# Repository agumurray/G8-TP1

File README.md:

# TdP-Grupo8-2025

**Robot resolutor de laberintos con EDU-CIAA**

Este proyecto consiste en el diseño y construcción de un robot móvil capaz de resolver laberintos físicos con paredes de manera autónoma. El sistema utiliza como controlador principal la **EDU-CIAA**, que gestiona los sensores y motores, y ejecuta algoritmos de navegación para alcanzar la salida sin necesidad de un mapa previo.

## Características principales

* Exploración autónoma de laberintos físicos.
* Algoritmos de resolución basados en estrategias clásicas (wall-following, Pledge, Trémaux).
* Plataforma móvil con dos motores DC controlados mediante un puente H L298N.
* Sensores ultrasónicos para la detección de paredes y obstáculos.
* Posibilidad de extender funcionalidades con:

  * Telemetría mediante ESP32 e interfaz web.
  * Algoritmos de búsqueda óptima (Flood Fill, A*).
  * Sensores adicionales como giroscopio para corrección de trayectoria.

## Tecnologías utilizadas

* **Hardware:**

  * EDU-CIAA (controlador central).
  * Motores DC con puente H L298N.
  * Sensores ultrasónicos HC-SR04.
  * Batería y sistema de alimentación dedicado.
  * (Opcional) ESP32 para telemetría y giroscopio.

* **Software:**

  * Lenguaje C para firmware en la EDU-CIAA.
  * Algoritmos de filtrado de señales y resolución de laberintos.
  * (Opcional) HTML/CSS/JavaScript para interfaz web de monitoreo.

## Objetivos

* **General:** Desarrollar un robot controlado por EDU-CIAA capaz de explorar físicamente un laberinto con paredes y alcanzar la salida mediante estrategias de navegación autónoma.

* **Primarios:**

  1. Diseñar la plataforma mecánica y de potencia (chasis, ruedas, transmisión, alimentación).
  2. Integrar sensado frontal para detección de paredes/obstáculos.
  3. Implementar un algoritmo de resolución de laberintos con información local.
  4. Validar el funcionamiento en laberintos de prueba con métricas definidas.

* **Secundarios:**

  1. Incorporar una interfaz web para recolectar telemetría.
  2. Implementar algoritmos de búsqueda óptima.
  3. Integrar un sensor giroscópico para corrección de maniobras.

## Integrantes

Este proyecto fue desarrollado por el **Grupo 8** en el marco de la materia **Taller de Proyecto I** en la Facultad de Ingeniería de la UNLP:

* Cabral Ramiro Nicolas
* Murray Agustín
* González Juan
* Mendoza Tomás

---

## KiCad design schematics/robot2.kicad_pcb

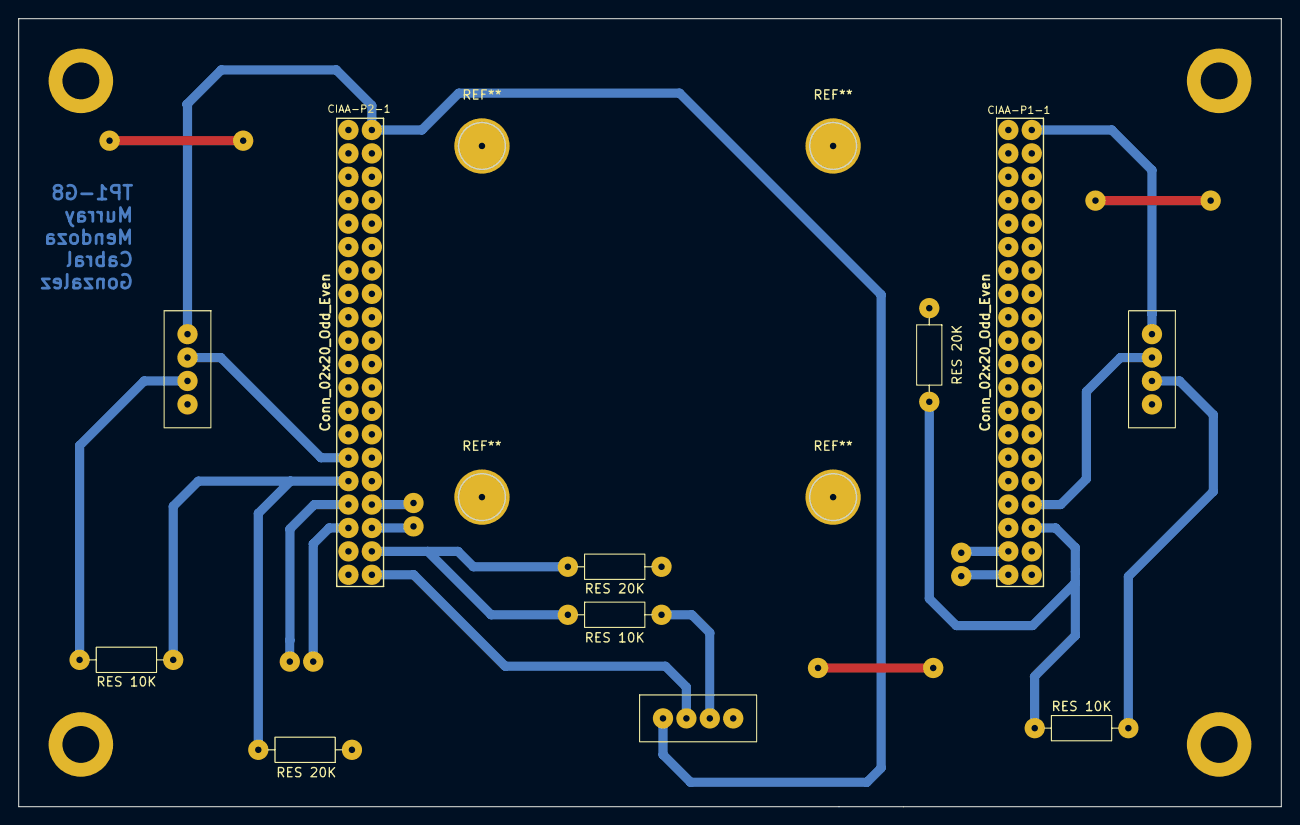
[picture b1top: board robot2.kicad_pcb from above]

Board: 2 copper layers, 137.0 x 85.5 mm, 11 parts (0 on the bottom side), 12 nets.

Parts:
CIAA-P1-1, CIAA-P2-1: Conn_02x20_Odd_Even; PIN_ARRAY_20X2
HC-SR04-1, HC-SR04-2, HC-SR04-3: HC-SR04
R2, R5: 20K; R_Axial_DIN0207_L6.3mm_D2.5mm_P10.16mm_Horizontal
RES 10K, RES 10K#2, RES 10K#3: 10K; R_Axial_DIN0207_L6.3mm_D2.5mm_P10.16mm_Horizontal
RES 20K: 20K; R_Axial_DIN0207_L6.3mm_D2.5mm_P10.16mm_Horizontal

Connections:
5VL: CIAA-P2-1.2 (5V), HC-SR04-1.1 (Vcc), HC-SR04-2.1 (Vcc)
5VR: CIAA-P1-1.2 (5V), HC-SR04-3.1 (Vcc)
GND: CIAA-P1-1.4 (GND), CIAA-P1-1.7 (GNDA), CIAA-P2-1.11 (GND), HC-SR04-1.4 (GND), HC-SR04-2.4 (GND), HC-SR04-3.4 (GND), R2.1, R5.1, RES 20K.1
GPIO0: CIAA-P2-1.29 (GPIO0), HC-SR04-1.2 (Trigger)
GPIO2: CIAA-P2-1.31 (GPIO2), R5.2, RES 10K#2.1
GPIO7: CIAA-P2-1.38 (GPIO7), RES 10K.1, RES 20K.2
GPIO8: CIAA-P2-1.40 (GPIO8), HC-SR04-2.2 (Trigger)
unnamed: HC-SR04-1.3 (Echo), RES 10K#2.2
unnamed: HC-SR04-2.3 (Echo), RES 10K.2
unnamed: HC-SR04-3.3 (Echo), RES 10K#3.2
TCOL2: CIAA-P1-1.34 (TCOL2), HC-SR04-3.2 (Trigger)
TFIL1: CIAA-P1-1.36 (TFIL1), R2.2, RES 10K#3.1

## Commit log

2025-09-25 fixes
2025-09-25 fix readme
2025-09-28 added schematic v2
2025-10-06 drivers hcsr04|l298n
2025-10-07 updated test program
2025-10-09 driver l298n reverse fix
2025-10-13 add project file structure
2025-10-16 added sensor pins
2025-10-19 stop front wall + new driver pins
2025-10-19 updt schematics
2025-10-23 new motor pins
2025-10-23 schematic fixes
2025-10-23 updated schematic
2025-10-23 sensor calibration
2025-10-27 updated pcb
2025-10-28 updated wall follower algorithm
2025-10-29 updated motor control
2025-11-02 updt pins on ide and sch
2025-11-11 update PCB
2025-11-17 updt pcb
2025-11-18 updt pcb gnd
2025-11-28 updt pcd
2025-11-29 updated left motor orientation
2025-12-12 updt wall follower
2026-02-24 last commit
